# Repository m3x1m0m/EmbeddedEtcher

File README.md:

# Embedded Etcher
Design files related to a photo-sensitive layering method etching machine
everyone can build to produce prototypes quickly at home or in the lab.

## Architecture 
The etching machine consists basically out of two parts. The
first part is a UV light, which is used to develop a photo-sensitive PCB. Once
this has been done.  The PCB has to be treated with sodium hydroxide (NaOH)
dissolved in water. This removes the UV-sensitive plastic, where it has been
tackeled by the light. 

The second part is the actual etching machine, which is designed to be
compatible to euro cards (and even bigger ones). The etching machine is either
filled with sodium persulfate (Na<sub>2</sub>S<sub>2</sub>O<sub>8</sub>) or
iron(III) chloride (FeCl<sub>3</sub>) dissolved in water of course.

## RedheadOS

One of the byproducts of this project is a small real-time OS, which is ment to run on embedded platforms. It is based on fixed priority scheduling and includes some nice accessories, so one does not always have to reinvent the wheel for every new project.  

## UV Light 

### Driver Extension Board

This PCB is made to fit the [Nucleo-F103RB](http://www.st.com/en/evaluation-tools/nucleo-f103rb.html)
development board from STM. Features:
* 64 LED driver stages.
* 6.4 A (0.1 A per stage) and 24 V max. input.
* 0.2 A max. and 350 mW dissipation max. per stage. Stages can be left floating if unused without
the threat of damaging the device.
* 10 Bit Digital-to-Analog Converter (DAC) to steer the driver combined with feedback amplification
to achieve a tremendously fine resolution.
* Optional potentiometer to set the current.
* Control loop to guarantee the desired current and respond quickly to changing the setpoint.
* 2 rotary encoders and 1 tactile switch.
* I2C header.
* SPI header.

  It is important to mention, that the resistors for the non-inverting amplifier
  in the feedback loop are optimized to result in a maximum current of 33 mA for
  3.3 V in order to achieve higher currents different resistor values have to be
  chosen.   

## Cuvette 

The cuvette can be handcrafted. It is possible to buy the five glass pieces need
at a glassers shop or to cut it oneself. The glass parts can be glued together with
silicon.

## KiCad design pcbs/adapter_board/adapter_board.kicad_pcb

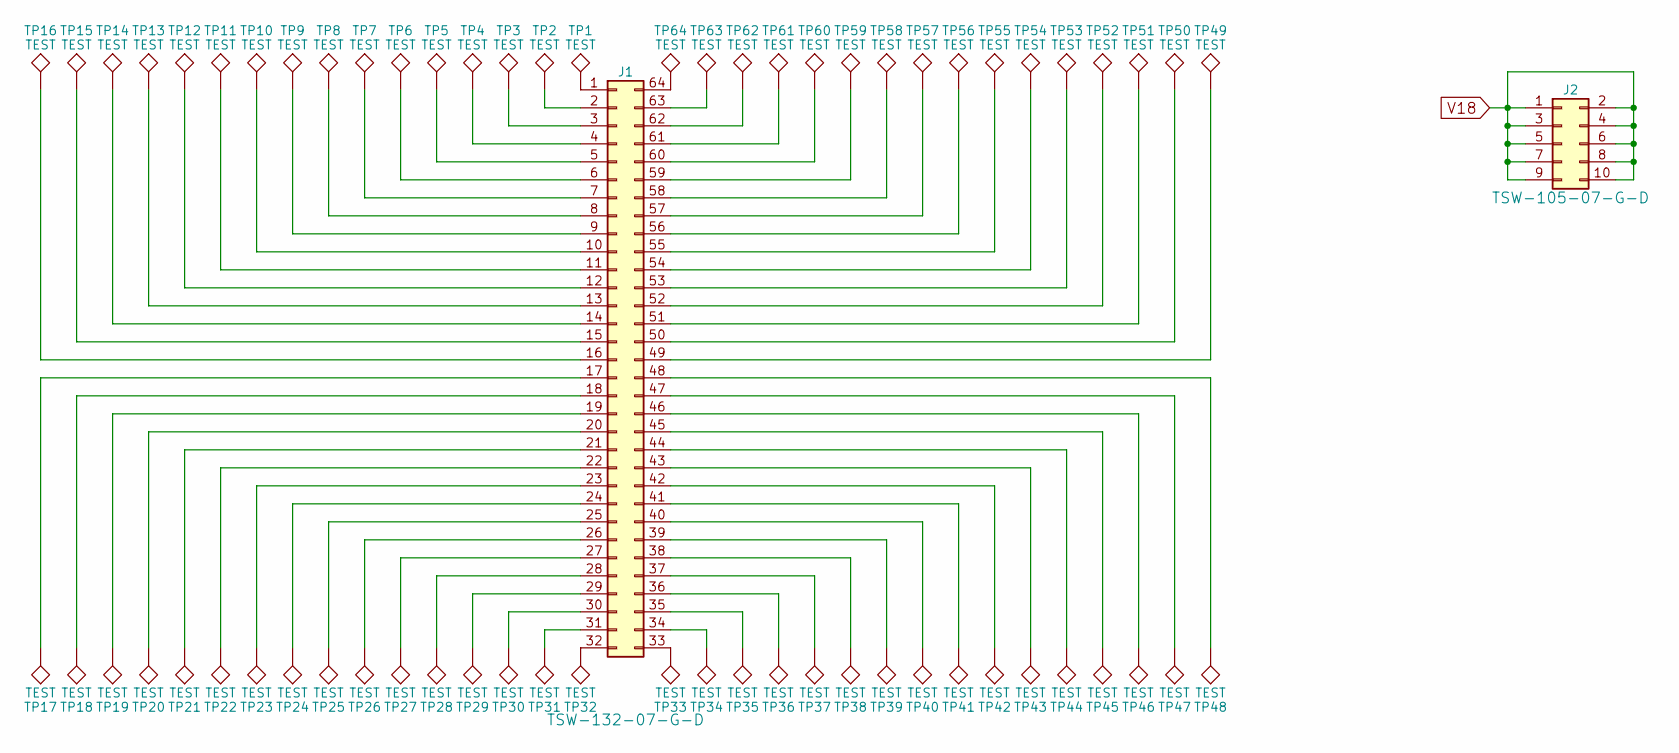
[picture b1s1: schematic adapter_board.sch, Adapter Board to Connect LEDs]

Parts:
J1: Conn_02x32_Counter_Clockwise; Pin_Header_Straight_2x32_Pitch2.54mm
J2: Conn_02x05_Odd_Even; Pin_Header_Straight_2x05_Pitch2.54mm
TP1, TP2, TP3, TP4, TP5, TP6, TP7, TP8, TP9, TP10, TP11, TP12, TP13, TP14, TP15, TP16, TP17, TP18, TP19, TP20, TP21, TP22, TP23, TP24, TP25, TP26, TP27, TP28, TP29, TP30, TP31, TP32, TP33, TP34, TP35, TP36, TP37, TP38, TP39, TP40, TP41, TP42, TP43, TP44, TP45, TP46, TP47, TP48, TP49, TP50, TP51, TP52, TP53, TP54, TP55, TP56, TP57, TP58, TP59, TP60, TP61, TP62, TP63, TP64: TEST; TP_SMD_2mmx5mm

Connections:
unnamed: J1.1, TP1.1
unnamed: J1.2, TP2.1
unnamed: J1.3, TP3.1
unnamed: J1.4, TP4.1
unnamed: J1.5, TP5.1
unnamed: J1.6, TP6.1
unnamed: J1.7, TP7.1
unnamed: J1.8, TP8.1
unnamed: J1.9, TP9.1
unnamed: J1.10, TP10.1
unnamed: J1.11, TP11.1
unnamed: J1.12, TP12.1
unnamed: J1.13, TP13.1
unnamed: J1.14, TP14.1
unnamed: J1.15, TP15.1
unnamed: J1.16, TP16.1
unnamed: J1.17, TP17.1
unnamed: J1.18, TP18.1
unnamed: J1.19, TP19.1
unnamed: J1.20, TP20.1
unnamed: J1.21, TP21.1
unnamed: J1.22, TP22.1
unnamed: J1.23, TP23.1
unnamed: J1.24, TP24.1
unnamed: J1.25, TP25.1
unnamed: J1.26, TP26.1
unnamed: J1.27, TP27.1
unnamed: J1.28, TP28.1
unnamed: J1.29, TP29.1
unnamed: J1.30, TP30.1
unnamed: J1.31, TP31.1
unnamed: J1.32, TP32.1
unnamed: J1.33, TP33.1
unnamed: J1.34, TP34.1
unnamed: J1.35, TP35.1
unnamed: J1.36, TP36.1
unnamed: J1.37, TP37.1
unnamed: J1.38, TP38.1
unnamed: J1.39, TP39.1
unnamed: J1.40, TP40.1
unnamed: J1.41, TP41.1
unnamed: J1.42, TP42.1
unnamed: J1.43, TP43.1
unnamed: J1.44, TP44.1
unnamed: J1.45, TP45.1
unnamed: J1.46, TP46.1
unnamed: J1.47, TP47.1
unnamed: J1.48, TP48.1
unnamed: J1.49, TP49.1
unnamed: J1.50, TP50.1
unnamed: J1.51, TP51.1
unnamed: J1.52, TP52.1
unnamed: J1.53, TP53.1
unnamed: J1.54, TP54.1
unnamed: J1.55, TP55.1
unnamed: J1.56, TP56.1
unnamed: J1.57, TP57.1
unnamed: J1.58, TP58.1
unnamed: J1.59, TP59.1
unnamed: J1.60, TP60.1
unnamed: J1.61, TP61.1
unnamed: J1.62, TP62.1
unnamed: J1.63, TP63.1
unnamed: J1.64, TP64.1
V18: J2.1, J2.2, J2.3, J2.4, J2.5, J2.6, J2.7, J2.8, J2.9, J2.10

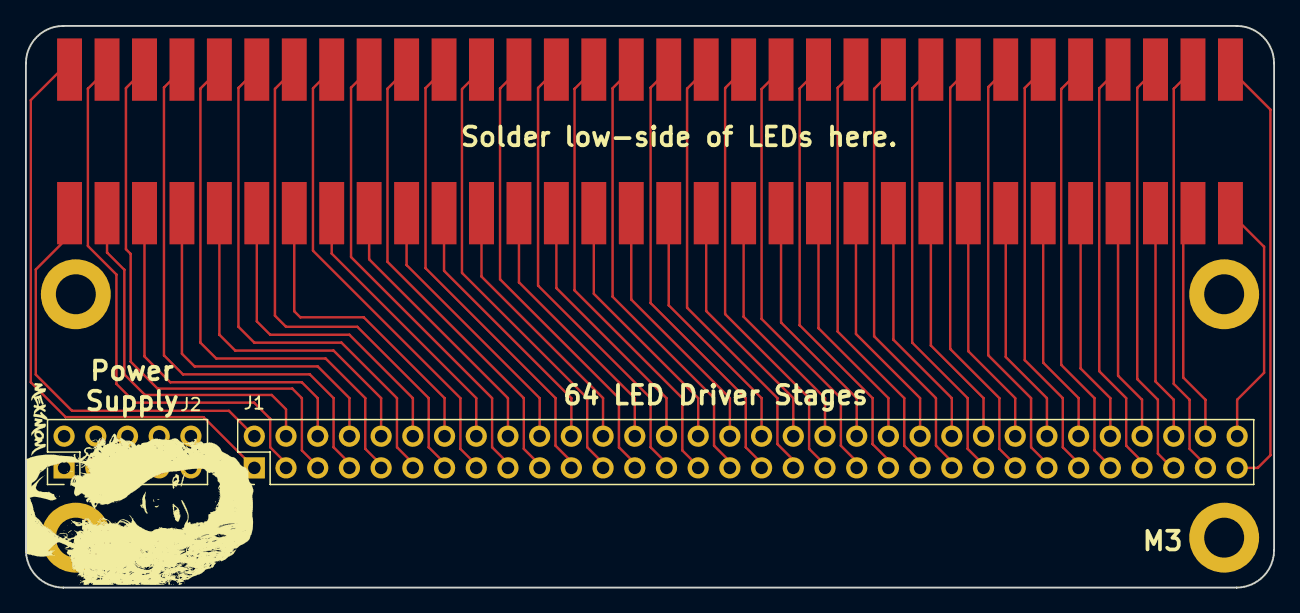
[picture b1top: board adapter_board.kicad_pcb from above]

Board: 2 copper layers, 100.0 x 45.0 mm, 66 parts (0 on the bottom side), 65 nets.

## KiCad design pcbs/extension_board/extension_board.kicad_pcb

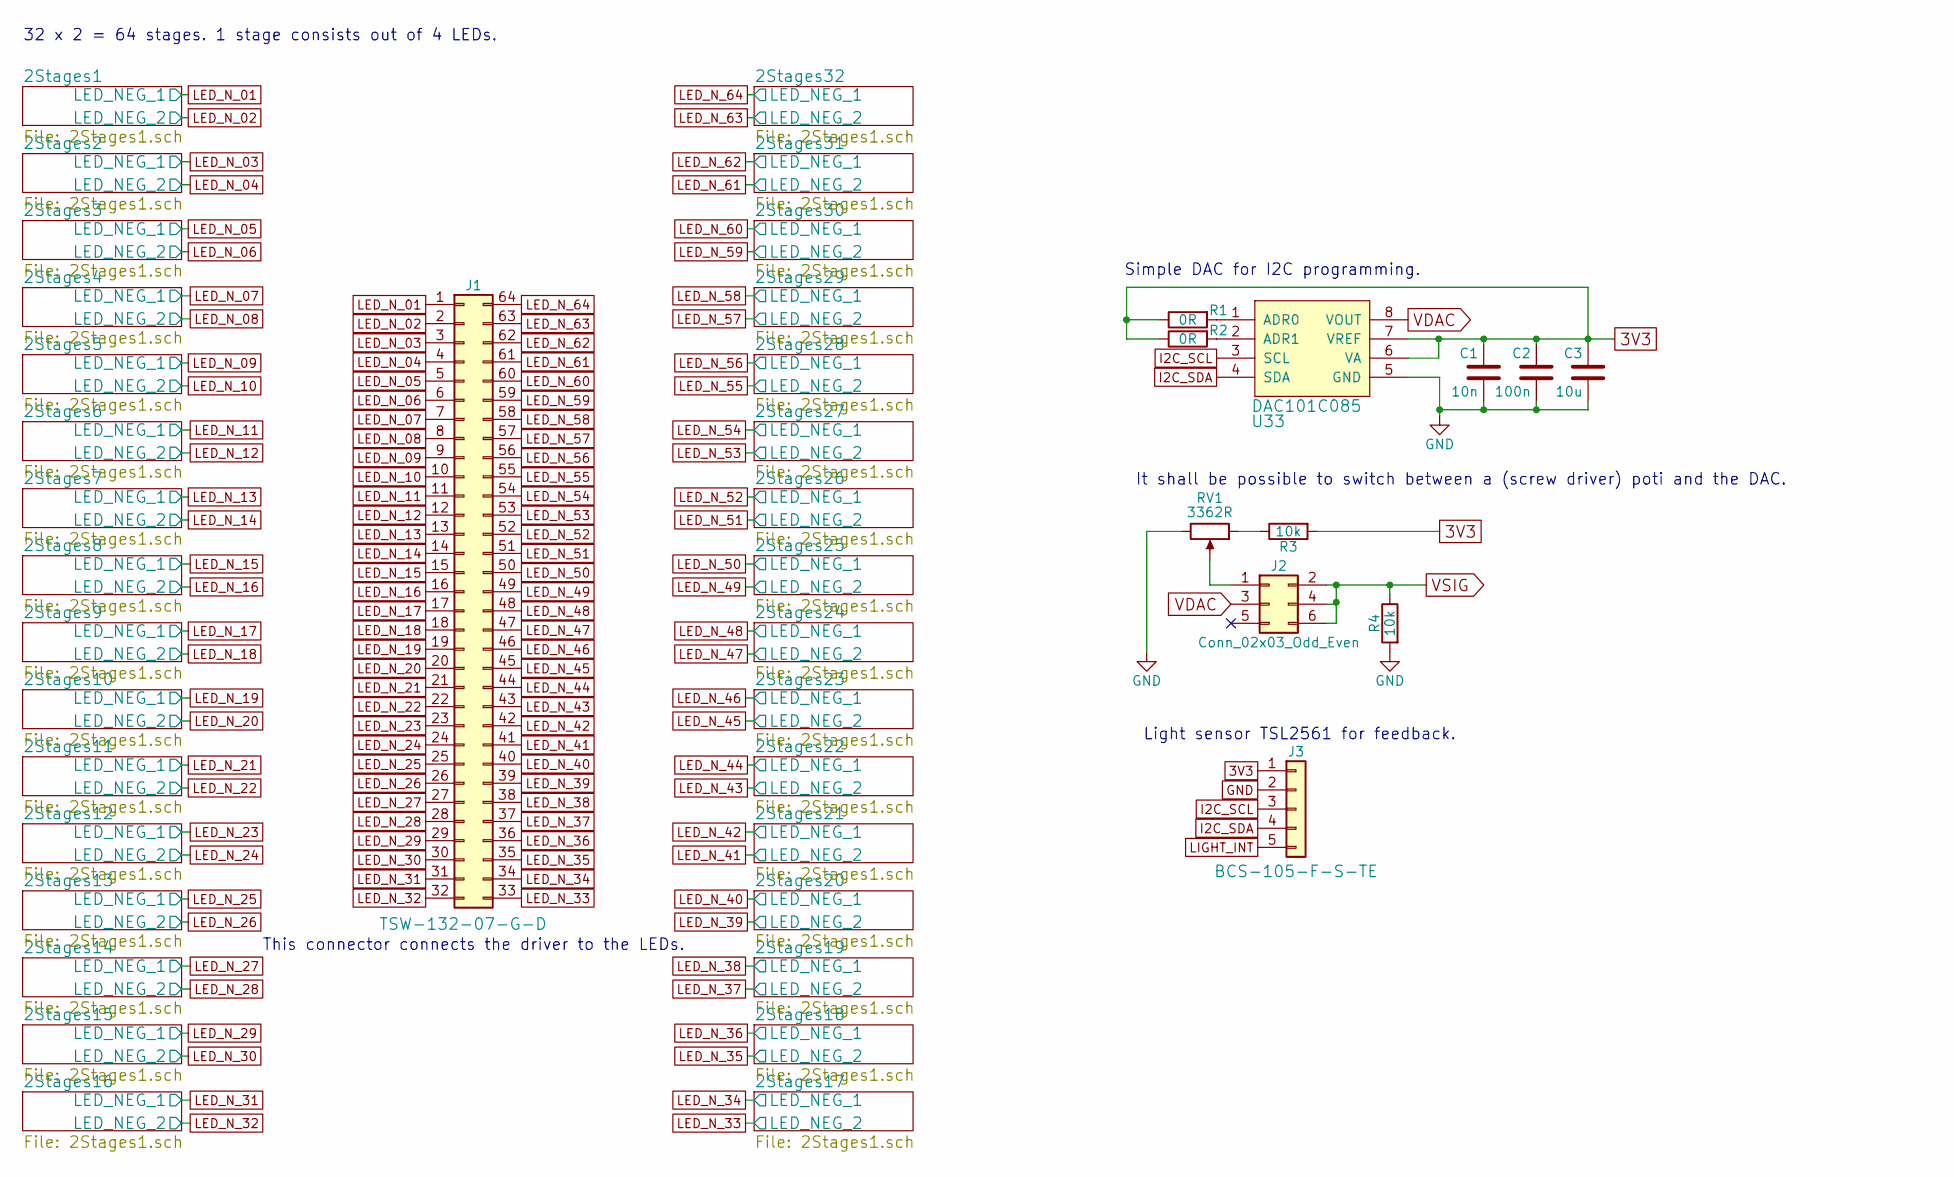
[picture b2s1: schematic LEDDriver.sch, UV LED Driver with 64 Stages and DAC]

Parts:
C1: 10n; R_0603; Digikey 311-1085-1-ND
C2: 100n; R_0603; Digikey 311-1088-1-ND
C3: 10u; R_0603; Digikey 490-6403-6-ND
J1: Conn_02x32_Counter_Clockwise; Pin_Header_Straight_2x32_Pitch2.54mm
J2: Conn_02x03_Odd_Even; Pin_Header_Straight_2x03_Pitch2.54mm
J3: Conn_01x05; Pin_Header_Straight_1x05_Pitch2.54mm
R1, R2: 0R; R_0603; Digikey 311-0.0GRCT-ND
R3, R4: 10k; R_0603; Digikey 311-10KGRCT-ND
RV1: 3362R; Burns_3362R; Digikey 3362R-103LF-ND
U33: DAC101C085; VSSOP-8_3.0x3.0mm_Pitch0.65mm; Digikey DAC101C085CIMM/NOPBCT-ND

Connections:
+3V3: C1.1, C2.1, C3.1, J3.1, R1.1, R2.1, R3.2, U33.6 (VA), U33.7 (VREF); also elsewhere on the board
GND: C1.2, C2.2, C3.2, J3.2, R4.2, RV1.3, U33.5 (GND); also elsewhere on the board
I2C_SCL: J3.3, U33.3 (SCL); also elsewhere on the board
I2C_SDA: J3.4, U33.4 (SDA); also elsewhere on the board
LED_N_01: J1.1; also elsewhere on the board
LED_N_02: J1.2; also elsewhere on the board
LED_N_03: J1.3; also elsewhere on the board
LED_N_04: J1.4; also elsewhere on the board
LED_N_05: J1.5; also elsewhere on the board
LED_N_06: J1.6; also elsewhere on the board
LED_N_07: J1.7; also elsewhere on the board
LED_N_08: J1.8; also elsewhere on the board
LED_N_09: J1.9; also elsewhere on the board
LED_N_10: J1.10; also elsewhere on the board
LED_N_11: J1.11; also elsewhere on the board
LED_N_12: J1.12; also elsewhere on the board
LED_N_13: J1.13; also elsewhere on the board
LED_N_14: J1.14; also elsewhere on the board
LED_N_15: J1.15; also elsewhere on the board
LED_N_16: J1.16; also elsewhere on the board
LED_N_17: J1.17; also elsewhere on the board
LED_N_18: J1.18; also elsewhere on the board
LED_N_19: J1.19; also elsewhere on the board
LED_N_20: J1.20; also elsewhere on the board
LED_N_21: J1.21; also elsewhere on the board
LED_N_22: J1.22; also elsewhere on the board
LED_N_23: J1.23; also elsewhere on the board
LED_N_24: J1.24; also elsewhere on the board
LED_N_25: J1.25; also elsewhere on the board
LED_N_26: J1.26; also elsewhere on the board
LED_N_27: J1.27; also elsewhere on the board
LED_N_28: J1.28; also elsewhere on the board
LED_N_29: J1.29; also elsewhere on the board
LED_N_30: J1.30; also elsewhere on the board
LED_N_31: J1.31; also elsewhere on the board
LED_N_32: J1.32; also elsewhere on the board
LED_N_33: J1.33; also elsewhere on the board
LED_N_34: J1.34; also elsewhere on the board
LED_N_35: J1.35; also elsewhere on the board
LED_N_36: J1.36; also elsewhere on the board
LED_N_37: J1.37; also elsewhere on the board
LED_N_38: J1.38; also elsewhere on the board
LED_N_39: J1.39; also elsewhere on the board
LED_N_40: J1.40; also elsewhere on the board
LED_N_41: J1.41; also elsewhere on the board
LED_N_42: J1.42; also elsewhere on the board
LED_N_43: J1.43; also elsewhere on the board
LED_N_44: J1.44; also elsewhere on the board
LED_N_45: J1.45; also elsewhere on the board
LED_N_46: J1.46; also elsewhere on the board
LED_N_47: J1.47; also elsewhere on the board
LED_N_48: J1.48; also elsewhere on the board
LED_N_49: J1.49; also elsewhere on the board
LED_N_50: J1.50; also elsewhere on the board
LED_N_51: J1.51; also elsewhere on the board
LED_N_52: J1.52; also elsewhere on the board
LED_N_53: J1.53; also elsewhere on the board
LED_N_54: J1.54; also elsewhere on the board
LED_N_55: J1.55; also elsewhere on the board
LED_N_56: J1.56; also elsewhere on the board
LED_N_57: J1.57; also elsewhere on the board
LED_N_58: J1.58; also elsewhere on the board
LED_N_59: J1.59; also elsewhere on the board
LED_N_60: J1.60; also elsewhere on the board
LED_N_61: J1.61; also elsewhere on the board
LED_N_62: J1.62; also elsewhere on the board
LED_N_63: J1.63; also elsewhere on the board
LED_N_64: J1.64; also elsewhere on the board
LIGHT_INT: J3.5; also elsewhere on the board
unnamed: J2.1, RV1.2
unnamed: R1.2, U33.1 (ADR0)
unnamed: R2.2, U33.2 (ADR1)
unnamed: R3.1, RV1.1
VDAC: J2.3, U33.8 (VOUT)
VSIG: J2.2, J2.4, J2.6, R4.1; also elsewhere on the board

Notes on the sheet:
It shall be possible to switch between a (screw driver) poti and the DAC.
Simple DAC for I2C programming.
Light sensor TSL2561 for feedback.
This connector connects the driver to the LEDs.
32 x 2 = 64 stages. 1 stage consists out of 4 LEDs.

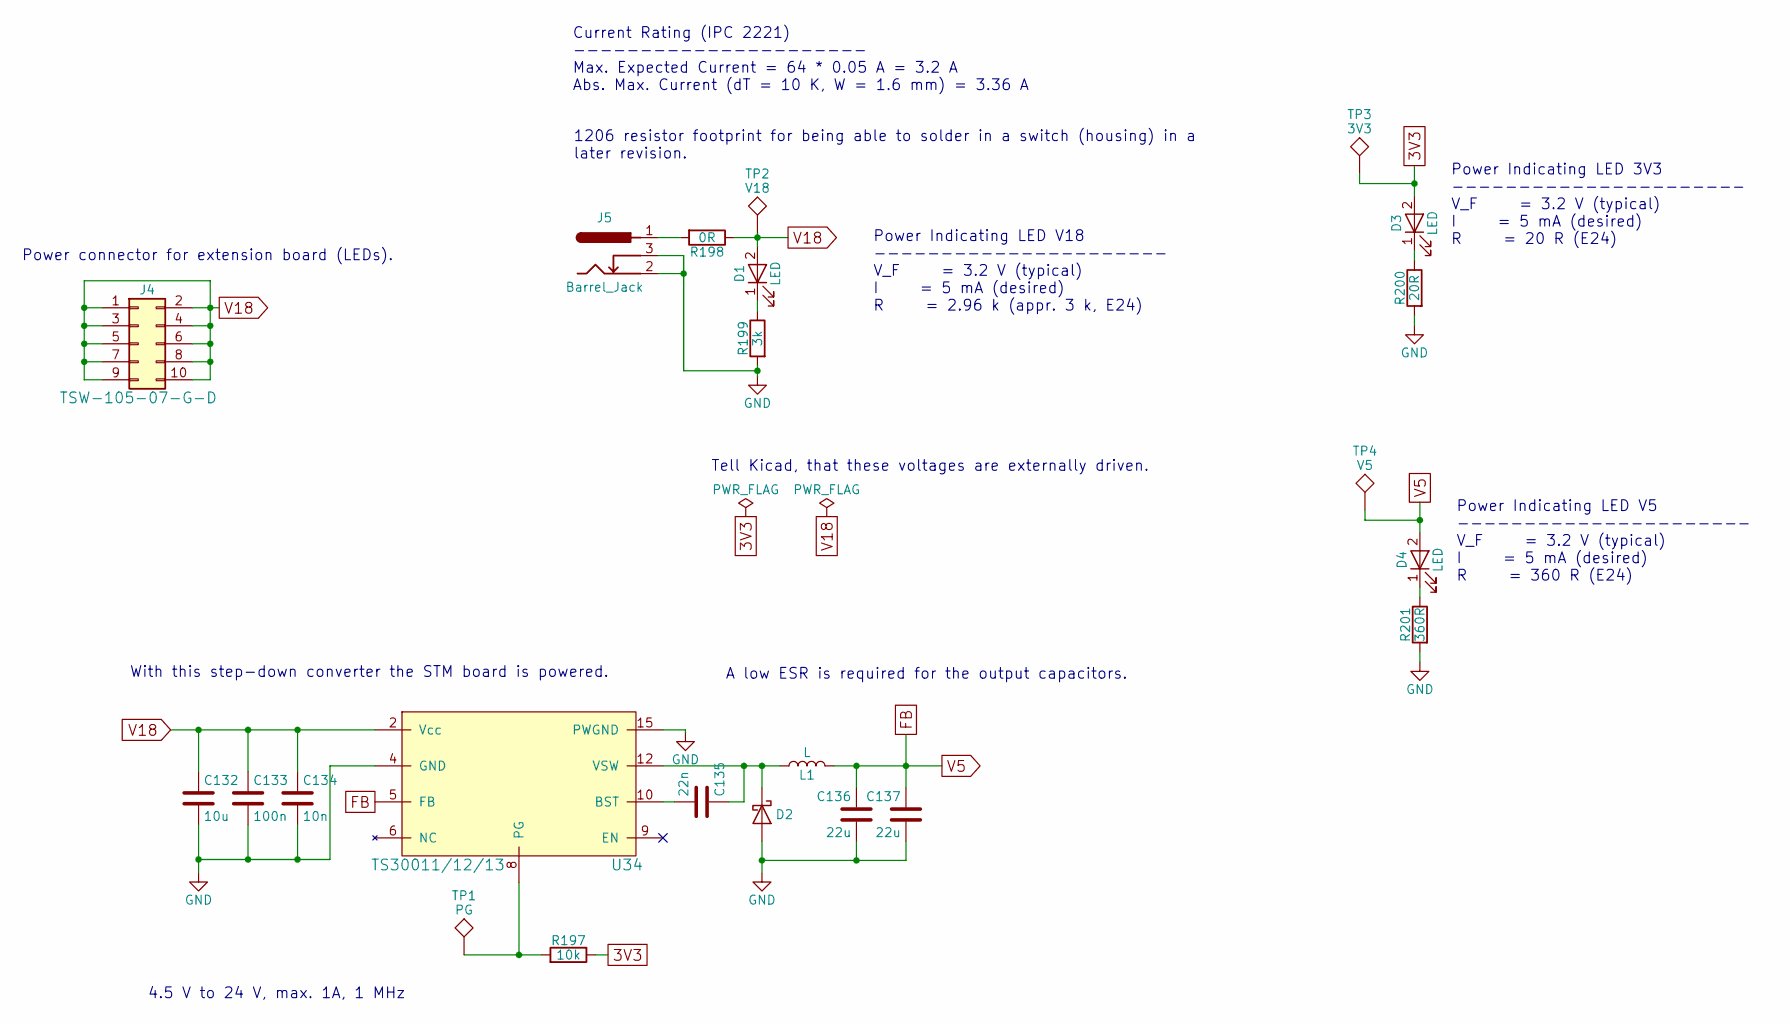
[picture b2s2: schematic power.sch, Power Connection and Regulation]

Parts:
C132: 10u; R_0603; Digikey 490-6403-6-ND
C133: 100n; R_0603; Digikey 311-1088-1-ND
C134: 10n; R_0603; Digikey 311-1085-1-ND
C135: 22n; R_0603; Digikey 1276-1104-1-ND
C136, C137: 22u; R_0603; Digikey 1276-2412-1-ND
D1, D3, D4: LED; LED_0603; Digikey 732-4971-1-ND
D2: D_Schottky; D_SOD-123; Digikey 1727-7332-1-ND
J4: Conn_02x05_Odd_Even; Pin_Header_Straight_2x05_Pitch2.54mm
J5: Barrel_Jack; BARREL_JACK
L1: L; WE-PD2-SMD-Power-Inductor; Digikey 732-1316-1-ND
R197: 10k; R_0603; Digikey 311-10KGRCT-ND
R198: 0R; R_1206; Digikey 311-0.0ERCT-ND
R199: 3k; R_0603; Digikey 311-3.0KGRCT-ND
R200: 20R; R_0603; Digikey 311-20GRCT-ND
R201: 360R; R_0603; Digikey 311-20GRCT-ND
TP1: PG; TP_SMD_quadr_1mm
TP2: V18; TP_SMD_quadr_1mm
TP3: 3V3; TP_SMD_quadr_1mm
TP4: V5; TP_SMD_quadr_1mm
U34: TS30011/12/13; QFN-16-1EP_3x3mm_Pitch0.5mm; Digikey TS30011-M050QFNRCT-ND

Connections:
+3V3: D3.2 (A), R197.1, TP3.1; also elsewhere on the board
E5V: C136.1, C137.1, D4.2 (A), L1.2, TP4.1, U34.5 (FB); also elsewhere on the board
GND: C132.2, C133.2, C134.2, C136.2, C137.2, D2.2 (A), J5.2, J5.3, R199.2, R200.2, R201.2, U34.4 (GND), U34.14 (PWGND), U34.15 (PWGND), U34.17 (Pad); also elsewhere on the board
unnamed: C135.1, D2.1 (K), L1.1, U34.1 (VSW), U34.12 (VSW), U34.13 (VSW), U34.16 (VSW)
unnamed: C135.2, U34.10 (BST)
unnamed: D1.1 (K), R199.1
unnamed: D3.1 (K), R200.1
unnamed: D4.1 (K), R201.1
unnamed: J5.1, R198.2
unnamed: R197.2, TP1.1, U34.8 (PG)
V18: C132.1, C133.1, C134.1, D1.2 (A), J4.1, J4.2, J4.3, J4.4, J4.5, J4.6, J4.7, J4.8, J4.9, J4.10, R198.1, TP2.1, U34.2 (Vcc), U34.3 (Vcc), U34.11 (Vcc); also elsewhere on the board

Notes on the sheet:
Power Indicating LED V18 ---------------------- V_F = 3.2 V (typical) I = 5 mA (desired) R = 2.96 k (appr. 3 k, E24)
A low ESR is required for the output capacitors.
Power Indicating LED V5 ---------------------- V_F = 3.2 V (typical) I = 5 mA (desired) R = 360 R (E24)
1206 resistor footprint for being able to solder in a switch (housing) in a later revision.
Power connector for extension board (LEDs).
With this step-down converter the STM board is powered.
Power Indicating LED 3V3 ---------------------- V_F = 3.2 V (typical) I = 5 mA (desired) R = 20 R (E24)
Tell Kicad, that these voltages are externally driven.
Current Rating (IPC 2221) ---------------------- Max. Expected Current = 64 * 0.05 A = 3.2 A Abs. Max. Current (dT = 10 K, W = 1.6 mm) = 3.36 A
4.5 V to 24 V, max. 1A, 1 MHz

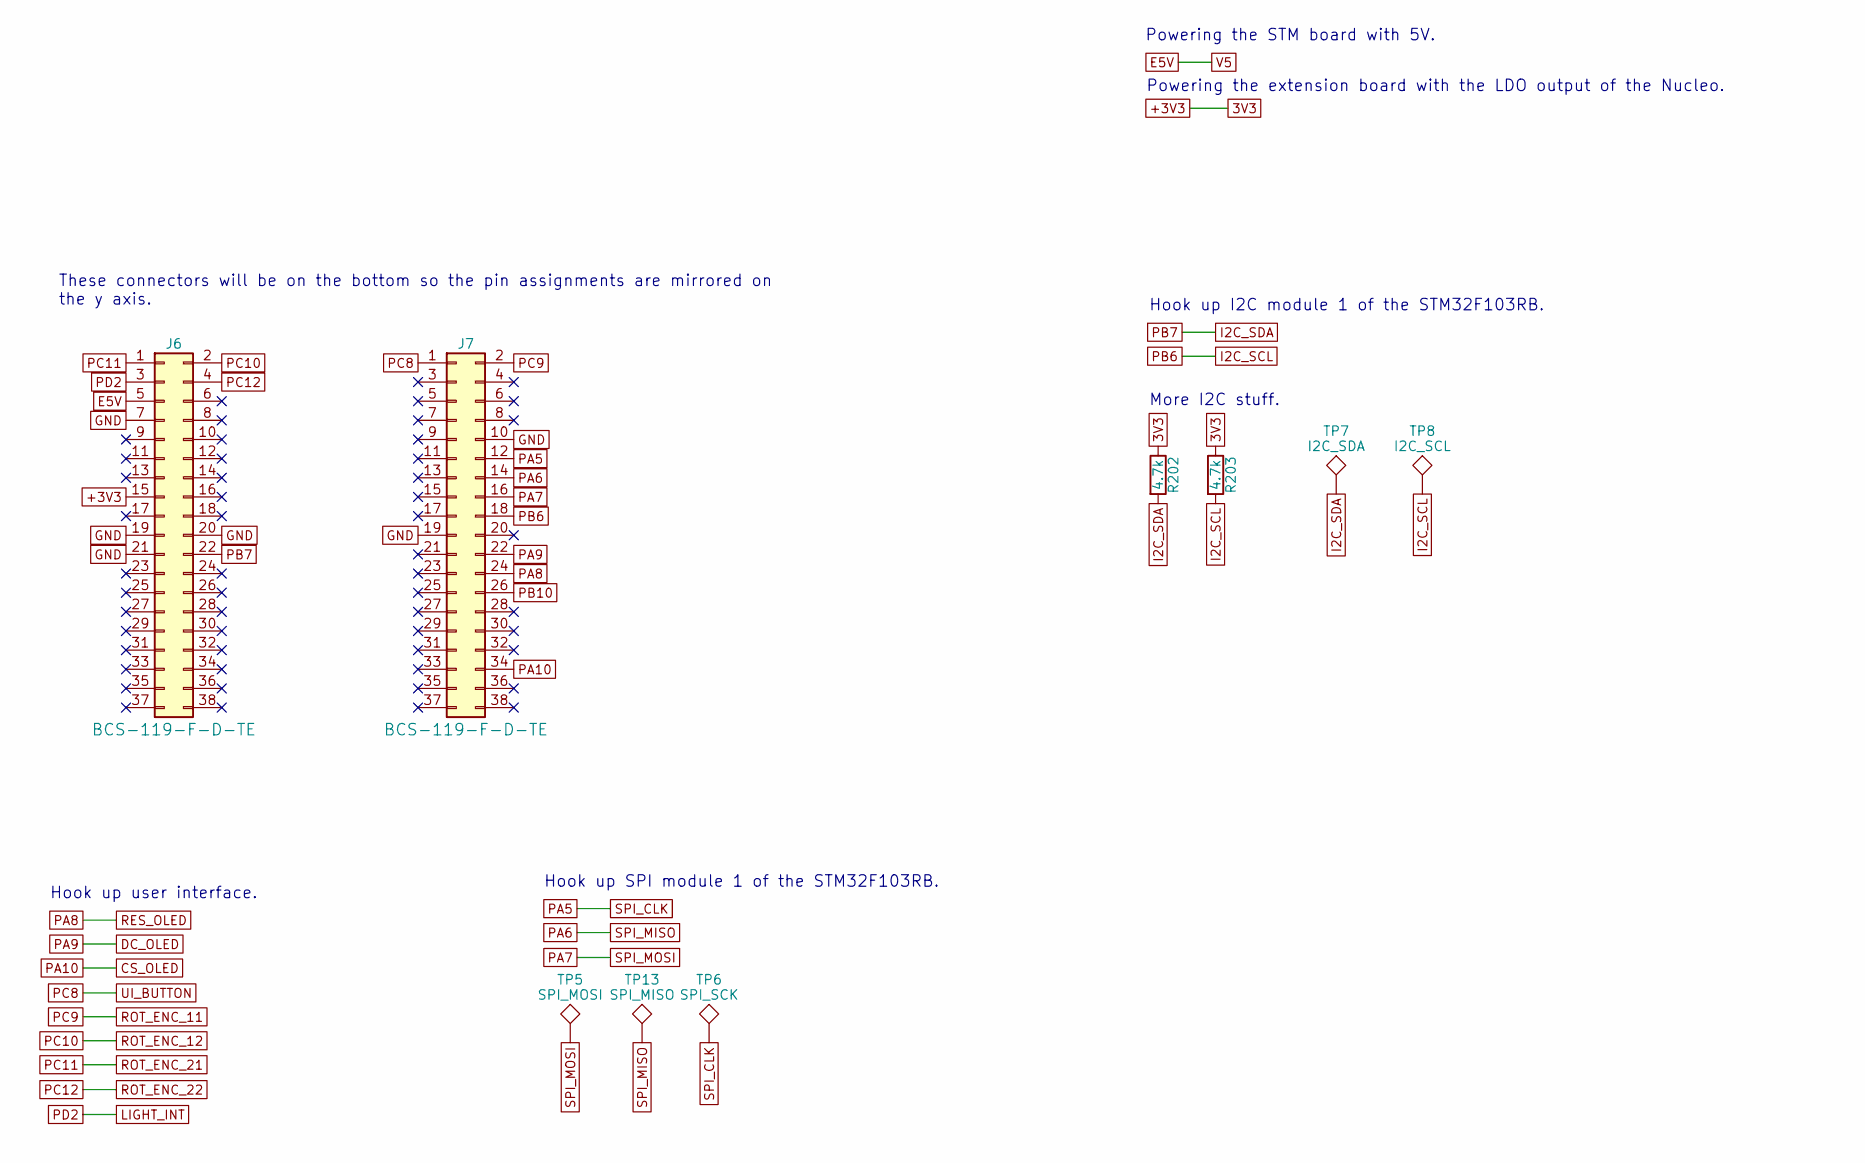
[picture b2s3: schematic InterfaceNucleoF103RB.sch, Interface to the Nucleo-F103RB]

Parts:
J6, J7: Conn_02x19_Odd_Even; Pin_Header_Straight_2x19_Pitch2.54mm
R202, R203: 4.7k; R_0603; Digikey 311-4.70KHRCT-ND
TP5: SPI_MOSI; TP_SMD_quadr_1mm
TP6: SPI_SCK; TP_SMD_quadr_1mm
TP7: I2C_SDA; TP_SMD_quadr_1mm
TP8: I2C_SCL; TP_SMD_quadr_1mm
TP13: SPI_MISO; TP_SMD_quadr_1mm

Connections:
+3V3: J6.15, R202.1, R203.1; also elsewhere on the board
CS_OLED: J7.34; also elsewhere on the board
DC_OLED: J7.22; also elsewhere on the board
E5V: J6.5; also elsewhere on the board
GND: J6.7, J6.19, J6.20, J6.21, J7.10, J7.19; also elsewhere on the board
I2C_SCL: J7.18, R203.2, TP8.1; also elsewhere on the board
I2C_SDA: J6.22, R202.2, TP7.1; also elsewhere on the board
LIGHT_INT: J6.3; also elsewhere on the board
PA5: J7.12, TP6.1; also elsewhere on the board
PA6: J7.14, TP13.1; also elsewhere on the board
PA7: J7.16, TP5.1; also elsewhere on the board
PA8: J7.24; also elsewhere on the board
PB10: J7.26; also elsewhere on the board
PC8: J7.1; also elsewhere on the board
PC9: J7.2; also elsewhere on the board
PC10: J6.2; also elsewhere on the board
PC11: J6.1; also elsewhere on the board
PC12: J6.4; also elsewhere on the board

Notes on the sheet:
These connectors will be on the bottom so the pin assignments are mirrored on the y axis.
Powering the STM board with 5V.
Hook up I2C module 1 of the STM32F103RB.
More I2C stuff.
Powering the extension board with the LDO output of the Nucleo.
Hook up SPI module 1 of the STM32F103RB.
Hook up user interface.

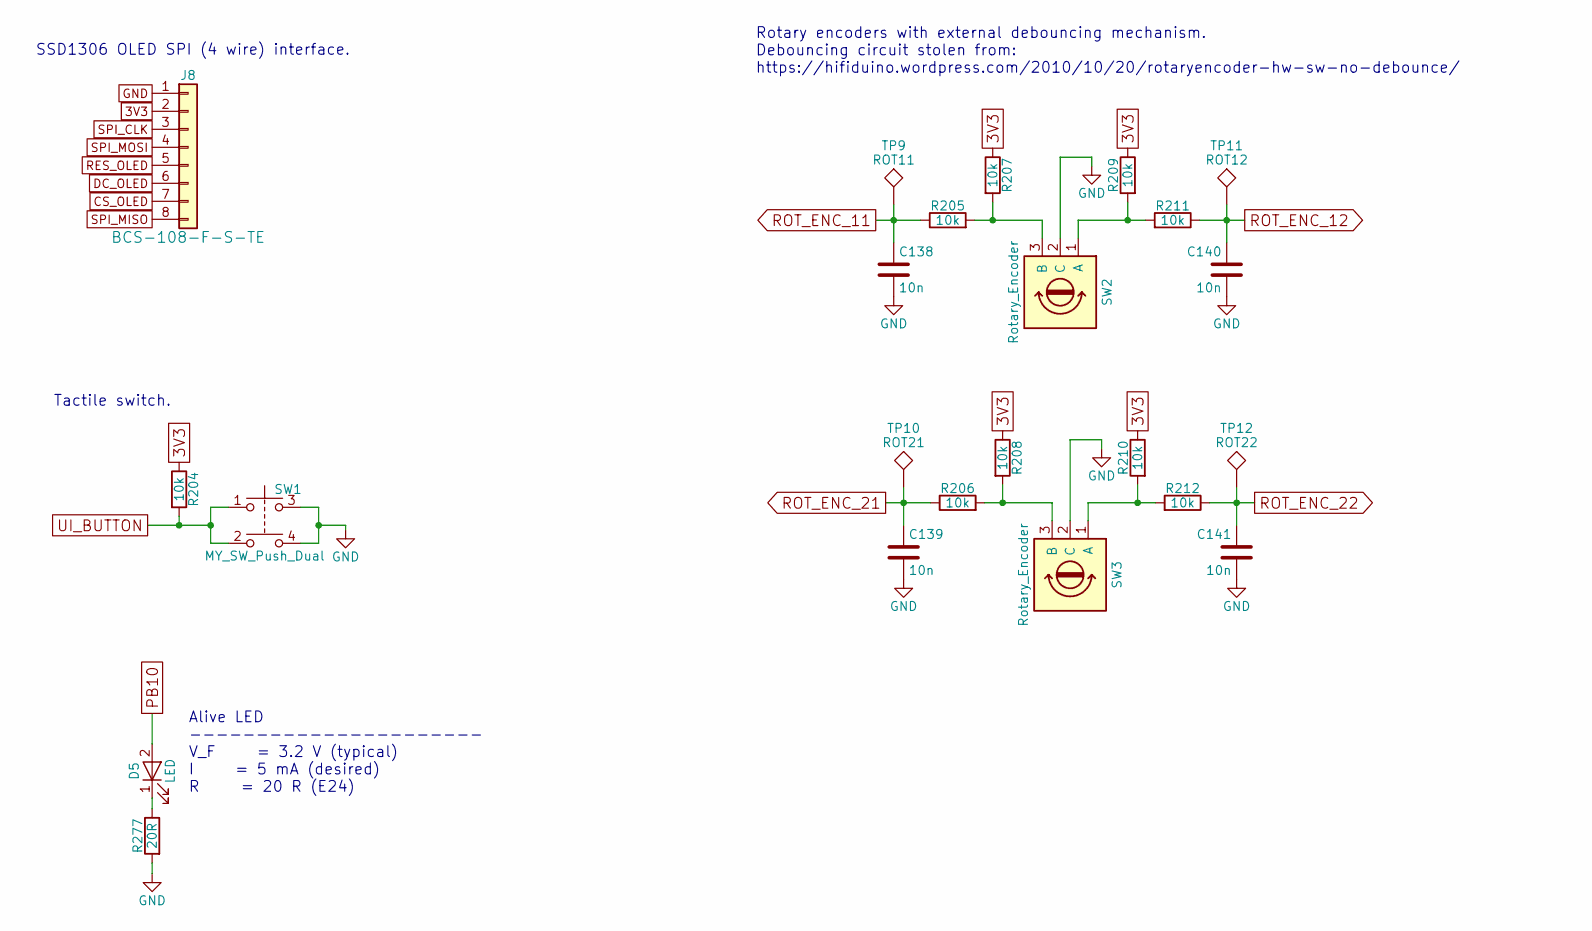
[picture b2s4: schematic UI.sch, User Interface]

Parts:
C138, C139, C140, C141: 10n; R_0603; Digikey 311-1085-1-ND
D5: LED; LED_0603; Digikey 732-4971-1-ND
J8: Conn_01x08; Pin_Header_Straight_1x08_Pitch2.54mm
R204, R205, R206, R207, R208, R209, R210, R211, R212: 10k; R_0603; Digikey 311-10KGRCT-ND
R277: 20R; R_0603; Digikey 1276-6153-1-ND
SW1: MY_SW_Push_Dual; SW_PUSH_TE_CONN_6x6; Digikey 450-1650-ND
SW2, SW3: Rotary_Encoder; ROT_ENC_EN12_TT_Electronics_No_Switch; Digikey 987-1399-ND
TP9: ROT11
TP10: ROT21
TP11: ROT12
TP12: ROT22

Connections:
+3V3: J8.2, R204.1, R207.1, R208.1, R209.1, R210.1; also elsewhere on the board
CS_OLED: J8.7; also elsewhere on the board
DC_OLED: J8.6; also elsewhere on the board
GND: C138.2, C139.2, C140.2, C141.2, J8.1, R277.2, SW1.3, SW1.4, SW2.2 (C), SW3.2 (C); also elsewhere on the board
unnamed: D5.1 (K), R277.1
unnamed: R205.2, R207.2, SW2.3 (B)
unnamed: R206.2, R208.2, SW3.3 (B)
unnamed: R209.2, R211.2, SW2.1 (A)
unnamed: R210.2, R212.2, SW3.1 (A)
PA5: J8.3; also elsewhere on the board
PA6: J8.8; also elsewhere on the board
PA7: J8.4; also elsewhere on the board
PA8: J8.5; also elsewhere on the board
PB10: D5.2 (A); also elsewhere on the board
PC8: R204.2, SW1.1, SW1.2; also elsewhere on the board
PC9: C138.1, R205.1, TP9.1; also elsewhere on the board
PC10: C140.1, R211.1, TP11.1; also elsewhere on the board
PC11: C139.1, R206.1, TP10.1; also elsewhere on the board
PC12: C141.1, R212.1, TP12.1; also elsewhere on the board

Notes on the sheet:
SSD1306 OLED SPI (4 wire) interface.
Rotary encoders with external debouncing mechanism. Debouncing circuit stolen from: https://hifiduino.wordpress.com/2010/10/20/rotaryencoder-hw-sw-no-debounce/
Tactile switch.
Alive LED ---------------------- V_F = 3.2 V (typical) I = 5 mA (desired) R = 20 R (E24)
